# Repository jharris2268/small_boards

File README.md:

# small_boards
small breakout pcbs

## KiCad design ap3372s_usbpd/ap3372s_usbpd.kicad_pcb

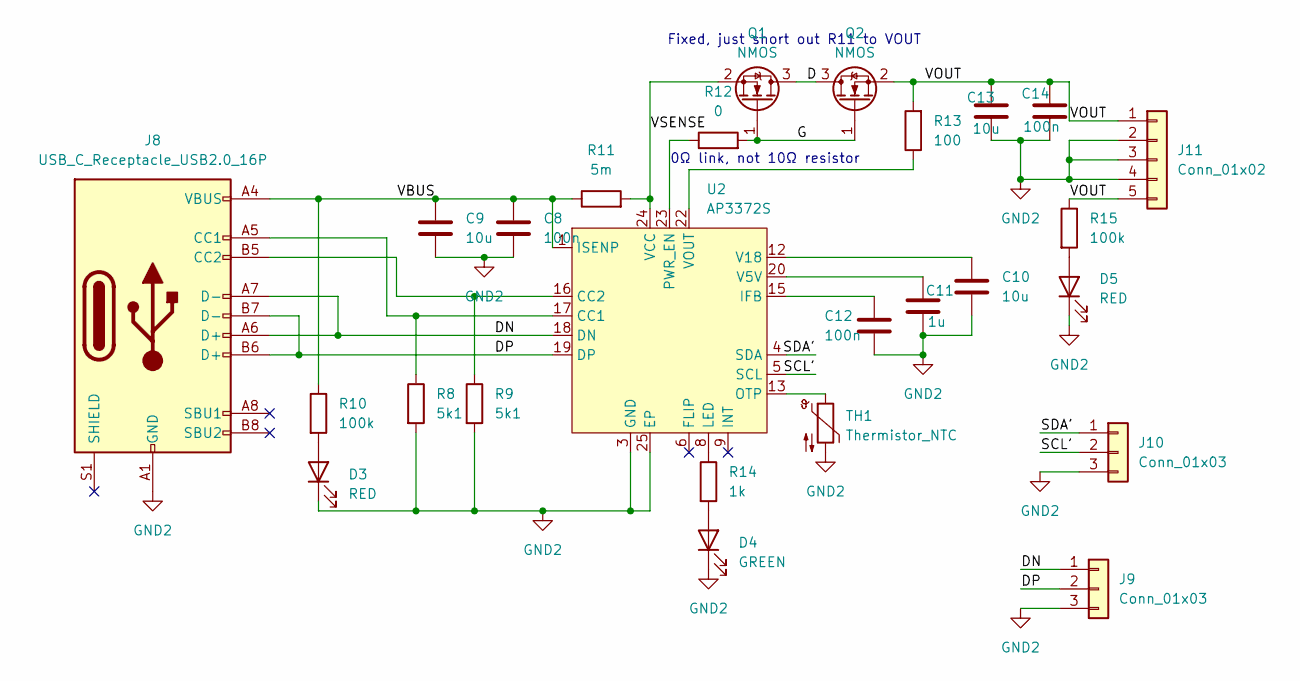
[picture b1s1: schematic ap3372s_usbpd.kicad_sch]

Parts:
C8, C12, C14: 100n; C_0805_2012Metric_Pad1.18x1.45mm_HandSolder
C9, C13: 10u; C_1206_3216Metric_Pad1.33x1.80mm_HandSolder
C10: 10u; C_0805_2012Metric_Pad1.18x1.45mm_HandSolder
C11: 1u; C_0805_2012Metric_Pad1.18x1.45mm_HandSolder
D3, D5: RED; LED_0805_2012Metric_Pad1.15x1.40mm_HandSolder
D4: GREEN; LED_0805_2012Metric_Pad1.15x1.40mm_HandSolder
J8: USB_C_Receptacle_USB2.0_16P; usb_c_connector
J9, J10: Conn_01x03; PinHeader_1x03_P2.54mm_Vertical
J11: Conn_01x02; PinHeader_1x05_P2.54mm_Vertical
Q1, Q2: NMOS; SOT-23
R8, R9: 5k1; R_0805_2012Metric_Pad1.20x1.40mm_HandSolder
R10, R15: 100k; R_0805_2012Metric_Pad1.20x1.40mm_HandSolder
R11: 5m; R_2512_6332Metric_Pad1.40x3.35mm_HandSolder
R12: 0; R_0805_2012Metric_Pad1.20x1.40mm_HandSolder
R13: 100; R_0805_2012Metric_Pad1.20x1.40mm_HandSolder
R14: 1k; R_0805_2012Metric_Pad1.20x1.40mm_HandSolder
TH1: Thermistor_NTC; R_0805_2012Metric_Pad1.20x1.40mm_HandSolder
U2: AP3372S; QFN-24-1EP_4x4mm_P0.5mm_EP2.6x2.6mm

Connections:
/D: Q1.3 (D), Q2.3 (D)
/DN: J8.A6 (D+), J8.A7 (D-), J9.1, U2.18 (DN)
/DP: J8.B6 (D+), J8.B7 (D-), J9.2, U2.19 (DP)
/G: Q1.1 (G), Q2.1 (G), R12.2
/SCL': J10.2, U2.5 (SCL)
/SDA': J10.1, U2.4 (SDA)
/VBUS: C8.1, C9.1, J8.A4 (VBUS), J8.A9 (VBUS), J8.B4 (VBUS), J8.B9 (VBUS), R10.1, R11.1, U2.1 (ISENP)
/VOUT: C13.1, C14.1, J11.1, J11.5, Q2.2 (S), R13.2, R15.1
/VSENSE: Q1.2 (S), R11.2, U2.24 (VCC)
GND2: C8.2, C9.2, C10.2, C11.2, C12.2, C13.2, C14.2, D3.1 (K), D4.1 (K), D5.1 (K), J8.A1 (GND), J8.A12 (GND), J8.B1 (GND), J8.B12 (GND), J9.3, J10.3, J11.2, J11.3, J11.4, R8.2, R9.2, TH1.2, U2.3 (GND), U2.25 (EP)
unnamed: D3.2 (A), R10.2
unnamed: D4.2 (A), R14.2
unnamed: D5.2 (A), R15.2
unnamed: J8.A5 (CC1), R8.1, U2.17 (CC1)
unnamed: J8.B5 (CC2), R9.1, U2.16 (CC2)
unnamed: C12.1, U2.15 (IFB)
unnamed: R14.1, U2.8 (LED)
unnamed: TH1.1, U2.13 (OTP)
unnamed: R12.1, U2.23 (PWR_EN)
unnamed: C11.1, U2.20 (V5V)
unnamed: C10.1, U2.12 (V18)
unnamed: R13.1, U2.22 (VOUT)

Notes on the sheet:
Fixed, just short out R11 to VOUT
0Ω link, not 10Ω resistor

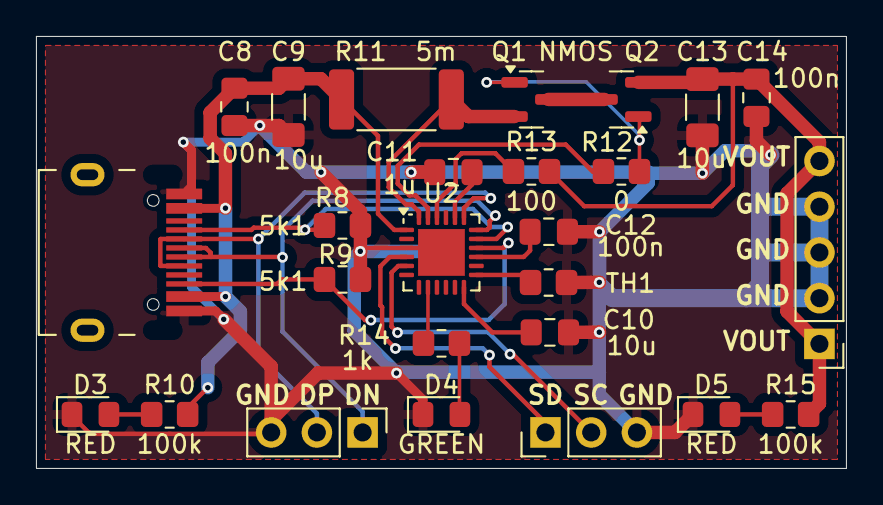
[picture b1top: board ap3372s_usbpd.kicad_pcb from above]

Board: 2 copper layers, 45.0 x 24.0 mm, 26 parts (0 on the bottom side), 22 nets.

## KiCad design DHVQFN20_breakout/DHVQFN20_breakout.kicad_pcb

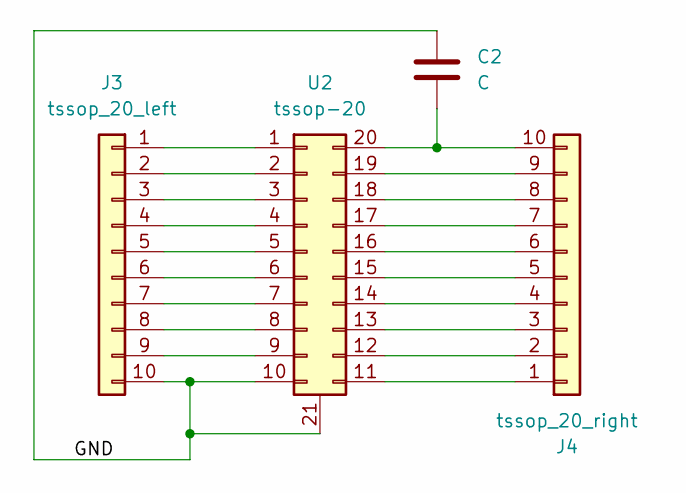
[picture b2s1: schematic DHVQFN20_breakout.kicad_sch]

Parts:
C2: C; C_0805_2012Metric_Pad1.18x1.45mm_HandSolder
J3: tssop_20_left; PinHeader_1x10_P2.54mm_Vertical
J4: tssop_20_right; PinHeader_1x10_P2.54mm_Vertical
U2: tssop-20; DHVQFN-20-1EP_2.5x4.5mm_P0.5mm_EP1x3mm

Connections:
/GND: C2.1, J3.10, U2.10, U2.21
unnamed: J3.1, U2.1
unnamed: J3.2, U2.2
unnamed: J3.3, U2.3
unnamed: J3.4, U2.4
unnamed: J3.5, U2.5
unnamed: J3.6, U2.6
unnamed: J3.7, U2.7
unnamed: J3.8, U2.8
unnamed: J3.9, U2.9
unnamed: J4.1, U2.11
unnamed: J4.2, U2.12
unnamed: J4.3, U2.13
unnamed: J4.4, U2.14
unnamed: J4.5, U2.15
unnamed: J4.6, U2.16
unnamed: J4.7, U2.17
unnamed: J4.8, U2.18
unnamed: J4.9, U2.19
unnamed: C2.2, J4.10, U2.20

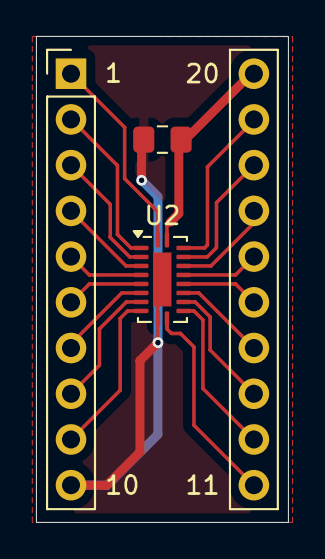
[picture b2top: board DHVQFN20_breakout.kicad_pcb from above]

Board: 2 copper layers, 14.0 x 27.0 mm, 4 parts (0 on the bottom side), 20 nets.

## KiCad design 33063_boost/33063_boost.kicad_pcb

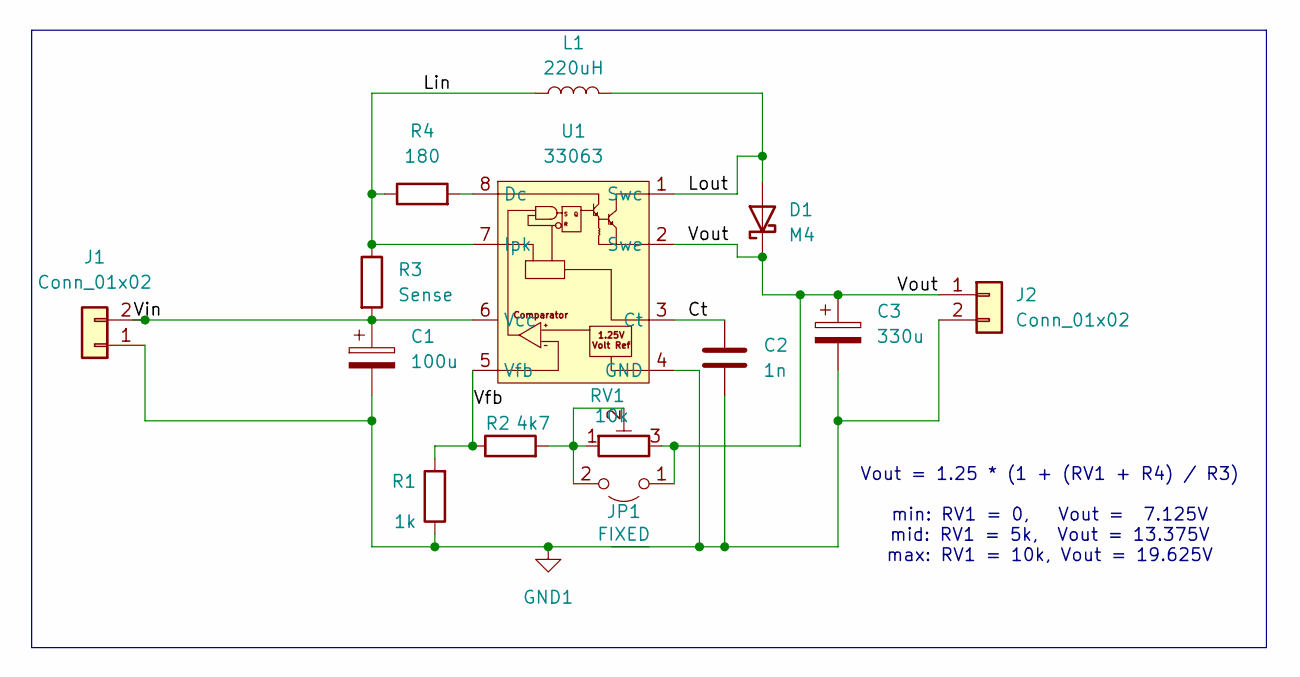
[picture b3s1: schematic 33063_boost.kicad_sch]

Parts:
C1: 100u; CP_Radial_D6.3mm_P2.50mm
C2: 1n; C_0805_2012Metric_Pad1.18x1.45mm_HandSolder
C3: 330u; CP_Radial_D6.3mm_P2.50mm
D1: M4; D_SMA_Handsoldering_with_symbol
J1, J2: Conn_01x02; sip_edge_2_no_slot
JP1: FIXED; SolderJumper-2_P1.3mm_Open_RoundedPad1.0x1.5mm
L1: 220uH; Inductor_CD54
R1: 1k; R_0805_2012Metric_Pad1.20x1.40mm_HandSolder
R2: 4k7; R_0805_2012Metric_Pad1.20x1.40mm_HandSolder
R3: Sense; LED_0805_2012Metric_Pad1.15x1.40mm_HandSolder
R4: 180; R_0805_2012Metric_Pad1.20x1.40mm_HandSolder
RV1: 10k; Potentiometer_Bourns_3296W_Vertical
U1: 33063; SOIC-8_3.9x4.9mm_P1.27mm

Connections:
/Ct: C2.1, U1.3 (Ct)
/Lin: L1.1, R3.1, R4.1, U1.7 (Ipk)
/Lout: D1.2 (A), L1.2, U1.1 (Swc)
/Vfb: R1.2, R2.1, U1.5 (Vfb)
/Vin: C1.1, J1.2, R3.2, U1.6 (Vcc)
/Vout: C3.1, D1.1 (K), J2.1, JP1.1 (A), RV1.3, U1.2 (Swe)
GND1: C1.2, C2.2, C3.2, J1.1, J2.2, R1.1, U1.4 (GND)
unnamed: JP1.2 (B), R2.2, RV1.1, RV1.2
unnamed: R4.2, U1.8 (Dc)

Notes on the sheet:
Vout = 1.25 * (1 + (RV1 + R4) / R3) min: RV1 = 0, Vout = 7.125V mid: RV1 = 5k, Vout = 13.375V max: RV1 = 10k, Vout = 19.625V

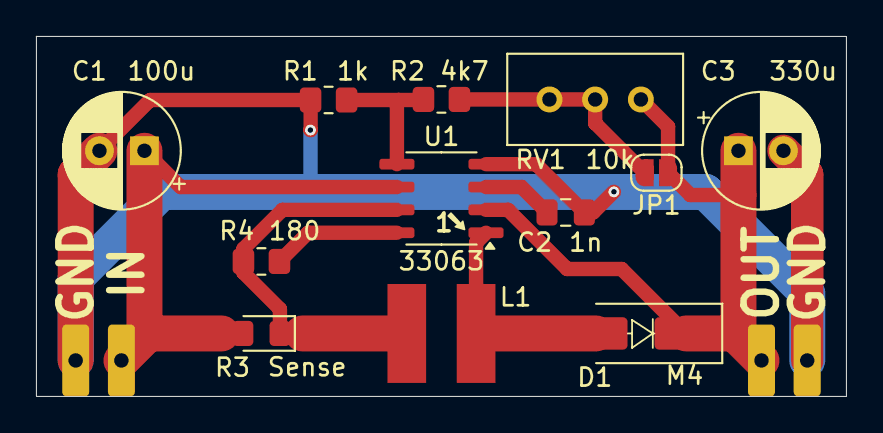
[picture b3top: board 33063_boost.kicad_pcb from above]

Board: 2 copper layers, 45.0 x 20.0 mm, 14 parts (0 on the bottom side), 9 nets.

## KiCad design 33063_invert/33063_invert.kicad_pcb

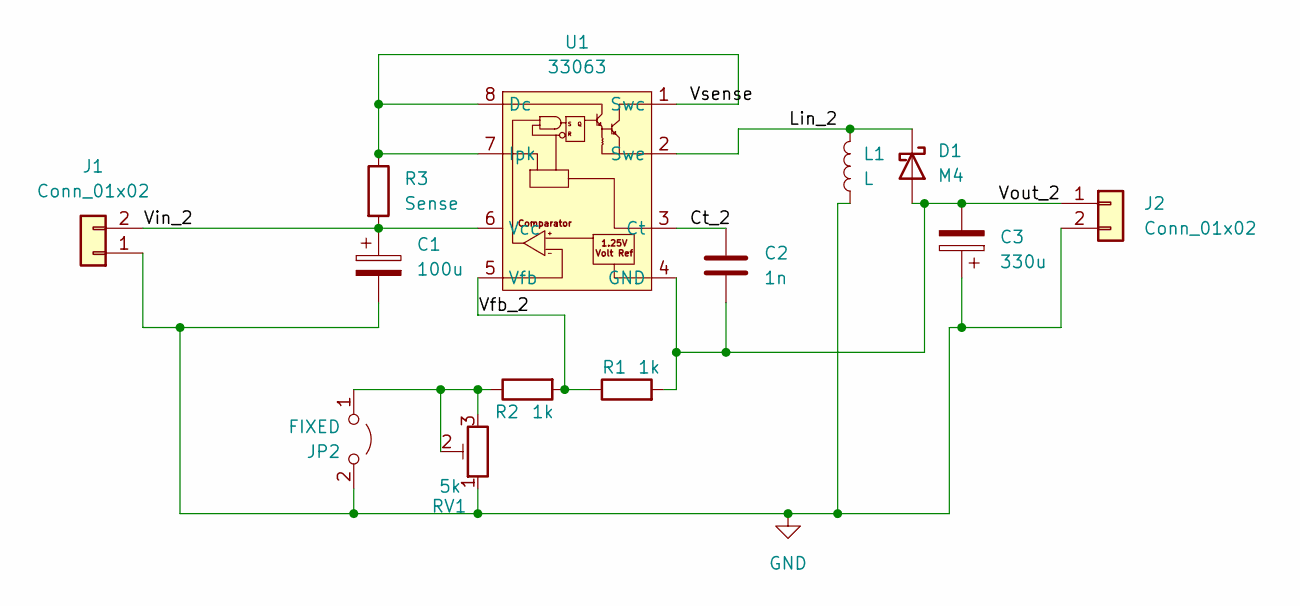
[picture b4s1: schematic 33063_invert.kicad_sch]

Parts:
C1: 100u; CP_Radial_D6.3mm_P2.50mm
C2: 1n; C_0805_2012Metric_Pad1.18x1.45mm_HandSolder
C3: 330u; CP_Radial_D6.3mm_P2.50mm
D1: M4; D_SMA_Handsoldering_with_symbol
J1, J2: Conn_01x02; sip_edge_2_no_slot
JP2: FIXED; SolderJumper-2_P1.3mm_Open_RoundedPad1.0x1.5mm
L1: L; Inductor_CD54
R1, R2: 1k; R_0805_2012Metric_Pad1.20x1.40mm_HandSolder
R3: Sense; R_0805_2012Metric_Pad1.20x1.40mm_HandSolder
RV1: 5k; Potentiometer_Bourns_3296W_Vertical
U1: 33063; SOIC-8_3.9x4.9mm_P1.27mm

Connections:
/Ct_2: C2.1, U1.3 (Ct)
/Lin_2: D1.1 (K), L1.2, U1.2 (Swe)
/Vfb_2: R1.1, R2.2, U1.5 (Vfb)
/Vin_2: C1.1, J1.2, R3.2, U1.6 (Vcc)
/Vout_2: C2.2, C3.2, D1.2 (A), J2.1, R1.2, U1.4 (GND)
/Vsense: R3.1, U1.1 (Swc), U1.7 (Ipk), U1.8 (Dc)
GND: C1.2, C3.1, J1.1, J2.2, JP2.2 (B), L1.1, RV1.1
unnamed: JP2.1 (A), R2.1, RV1.2, RV1.3

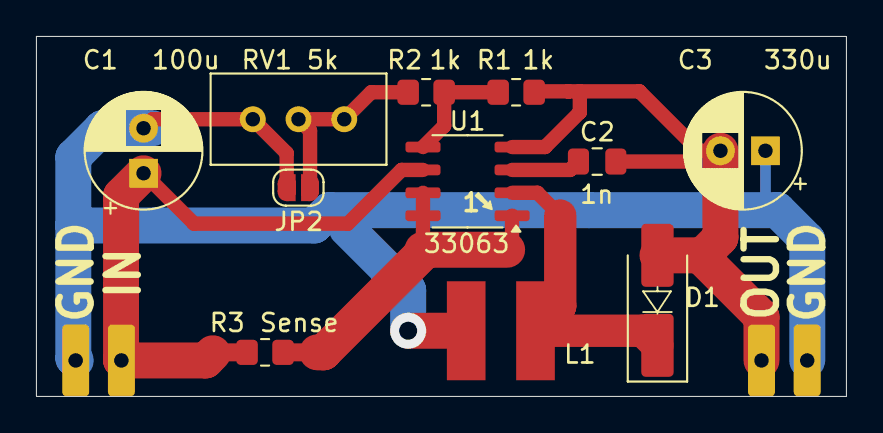
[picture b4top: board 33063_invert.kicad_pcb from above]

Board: 2 copper layers, 45.0 x 20.0 mm, 13 parts (0 on the bottom side), 8 nets.

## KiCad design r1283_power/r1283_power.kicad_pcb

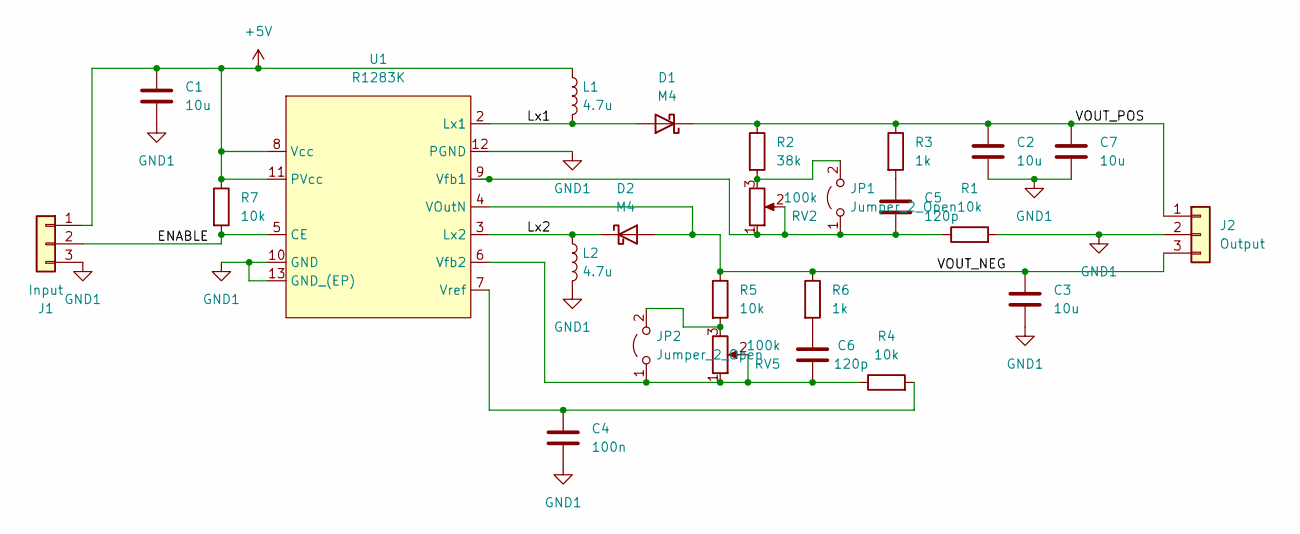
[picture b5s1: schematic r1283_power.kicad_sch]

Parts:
C1, C2, C3, C7: 10u; C_0805_2012Metric_Pad1.18x1.45mm_HandSolder
C4: 100n; C_0805_2012Metric_Pad1.18x1.45mm_HandSolder
C5, C6: 120p; C_0805_2012Metric_Pad1.18x1.45mm_HandSolder
D1, D2: M4; D_SMA_Handsoldering
J1: Input; sip_edge_3
J2: Output; sip_edge_3
JP1, JP2: Jumper_2_Open; SolderJumper-2_P1.3mm_Open_RoundedPad1.0x1.5mm
L1, L2: 4.7u; L_Wuerth_HCI-5040
R1, R4, R5, R7: 10k; R_0805_2012Metric_Pad1.20x1.40mm_HandSolder
R2: 38k; R_0805_2012Metric_Pad1.20x1.40mm_HandSolder
R3, R6: 1k; R_0805_2012Metric_Pad1.20x1.40mm_HandSolder
RV2, RV5: 100k; Potentiometer_Bourns_3296W_Vertical
U1: R1283K; DFN-12-1EP_3x3mm_P0.5mm_EP1.6x2.5mm

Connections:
+5V: C1.1, J1.1, L1.1, R7.1, U1.8 (Vcc), U1.11 (PVcc)
/ENABLE: J1.2, R7.2, U1.5 (CE)
/Lx1: D1.2 (A), L1.2, U1.2 (Lx1)
/Lx2: D2.1 (K), L2.1, U1.3 (Lx2)
/VOUT_NEG: C3.1, D2.2 (A), J2.3, R5.1, R6.1, U1.4 (VOutN)
/VOUT_POS: C2.1, C7.1, D1.1 (K), J2.1, R2.1, R3.1
GND1: C1.2, C2.2, C3.2, C4.2, C7.2, J1.3, J2.2, L2.2, R1.2, U1.10 (GND), U1.12 (PGND), U1.13 (GND_(EP))
unnamed: C5.1, R3.2
unnamed: C6.1, R6.2
unnamed: C5.2, JP1.1 (A), R1.1, RV2.1, RV2.2, U1.9 (Vfb1)
unnamed: JP1.2 (B), R2.2, RV2.3
unnamed: C6.2, JP2.1 (A), R4.1, RV5.1, RV5.2, U1.6 (Vfb2)
unnamed: JP2.2 (B), R5.2, RV5.3
unnamed: C4.1, R4.2, U1.7 (Vref)

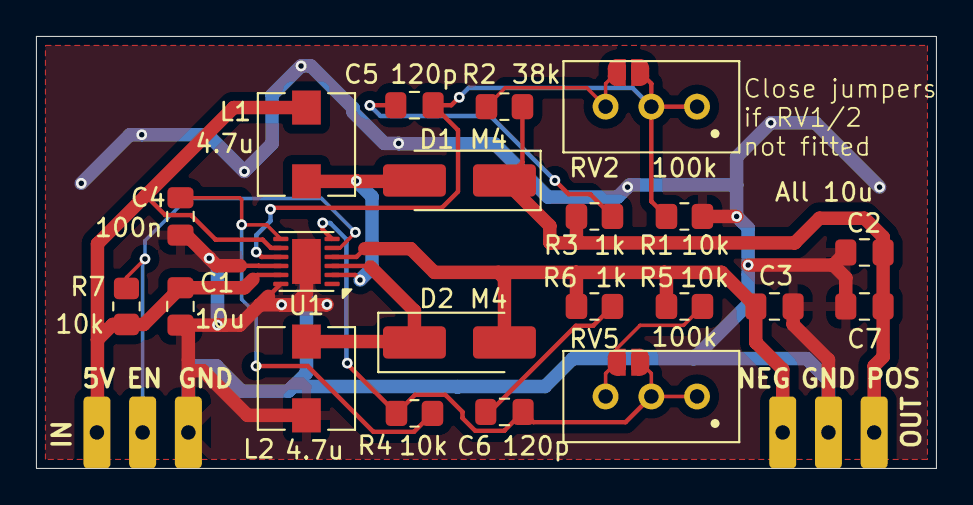
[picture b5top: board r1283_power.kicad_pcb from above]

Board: 2 copper layers, 50.0 x 24.0 mm, 25 parts (1 on the bottom side), 14 nets.

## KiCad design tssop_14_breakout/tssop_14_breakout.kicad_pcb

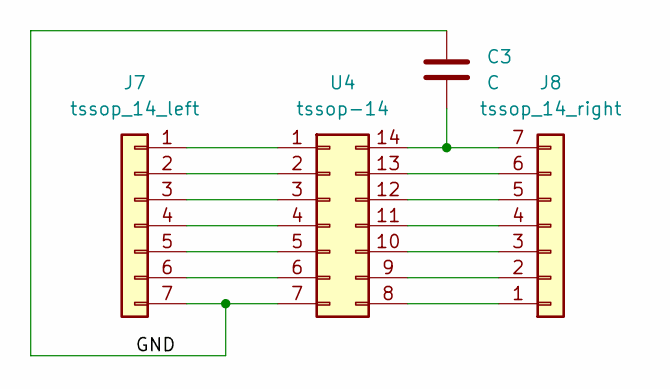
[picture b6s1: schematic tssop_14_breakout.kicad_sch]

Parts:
C3: C; C_0805_2012Metric_Pad1.18x1.45mm_HandSolder
J7: tssop_14_left; PinHeader_1x07_P2.54mm_Vertical
J8: tssop_14_right; PinHeader_1x07_P2.54mm_Vertical
U4: tssop-14; TSSOP-14_4.4x5mm_P0.65mm

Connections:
/GND: C3.1, J7.7, U4.7
unnamed: J7.1, U4.1
unnamed: J7.2, U4.2
unnamed: J7.3, U4.3
unnamed: J7.4, U4.4
unnamed: J7.5, U4.5
unnamed: J7.6, U4.6
unnamed: J8.1, U4.8
unnamed: J8.2, U4.9
unnamed: J8.3, U4.10
unnamed: J8.4, U4.11
unnamed: J8.5, U4.12
unnamed: J8.6, U4.13
unnamed: C3.2, J8.7, U4.14

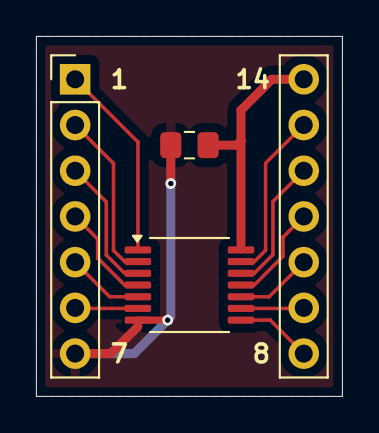
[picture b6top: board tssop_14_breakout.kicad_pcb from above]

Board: 2 copper layers, 17.0 x 20.0 mm, 4 parts (0 on the bottom side), 14 nets.

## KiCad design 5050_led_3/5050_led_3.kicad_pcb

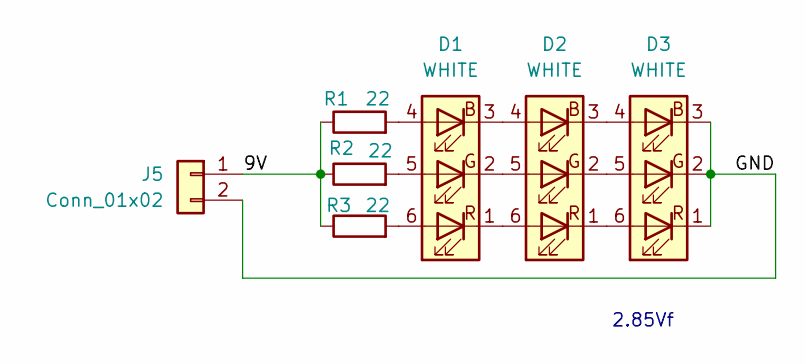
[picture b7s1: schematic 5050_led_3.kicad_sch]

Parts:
D1, D2, D3: WHITE; LED_RGB_5050-6
J5: Conn_01x02; sip_edge_2_no_slot
R1, R2, R3: 22; R_0805_2012Metric_Pad1.20x1.40mm_HandSolder

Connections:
/9V: J5.1, R1.1, R2.1, R3.1
/GND: D3.1 (RK), D3.2 (GK), D3.3 (BK), J5.2
unnamed: D1.4 (BA), R1.2
unnamed: D1.3 (BK), D2.4 (BA)
unnamed: D1.5 (GA), R2.2
unnamed: D1.2 (GK), D2.5 (GA)
unnamed: D1.6 (RA), R3.2
unnamed: D1.1 (RK), D2.6 (RA)
unnamed: D2.3 (BK), D3.4 (BA)
unnamed: D2.2 (GK), D3.5 (GA)
unnamed: D2.1 (RK), D3.6 (RA)

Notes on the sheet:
2.85Vf

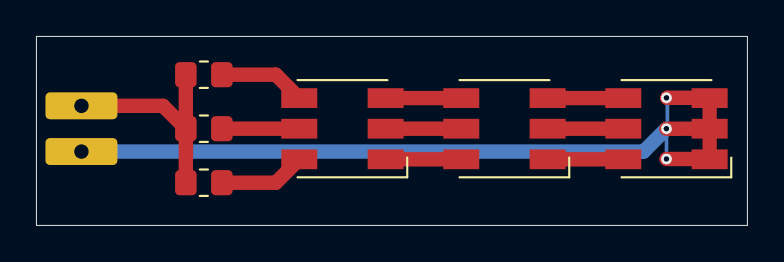
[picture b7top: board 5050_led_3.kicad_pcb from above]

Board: 2 copper layers, 39.5 x 10.5 mm, 7 parts (0 on the bottom side), 11 nets.

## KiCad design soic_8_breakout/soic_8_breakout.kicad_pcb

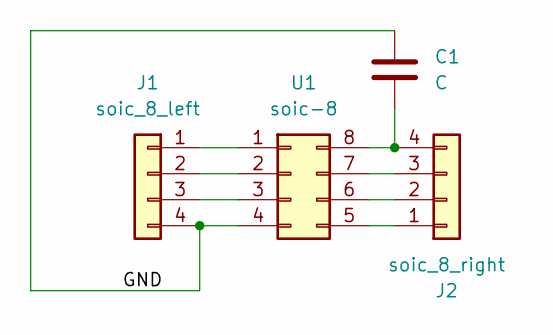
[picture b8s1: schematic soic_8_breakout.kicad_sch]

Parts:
C1: C; C_0805_2012Metric_Pad1.18x1.45mm_HandSolder
J1: soic_8_left; PinHeader_1x04_P2.54mm_Vertical
J2: soic_8_right; PinHeader_1x04_P2.54mm_Vertical
U1: soic-8; SOIC-8_3.9x4.9mm_P1.27mm

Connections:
/GND: C1.1, J1.4, U1.4
unnamed: J1.1, U1.1
unnamed: J1.2, U1.2
unnamed: J1.3, U1.3
unnamed: J2.1, U1.5
unnamed: J2.2, U1.6
unnamed: J2.3, U1.7
unnamed: C1.2, J2.4, U1.8

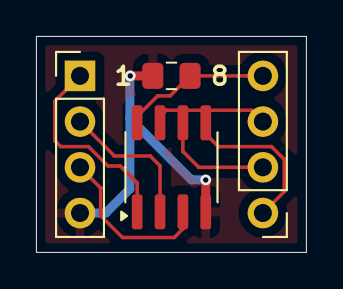
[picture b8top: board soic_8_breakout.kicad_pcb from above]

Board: 2 copper layers, 15.0 x 12.0 mm, 4 parts (0 on the bottom side), 8 nets.

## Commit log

2025-01-06 inital commit
2025-01-06 added gerbers
2025-01-06 copied in 33063 and led boards
2025-01-07 tidied up ap3372 board
2025-01-20 added DFN breakout changed trim pot type in 33063_boost, 33063_invert, r1283_power boards fixed error in 33063_boost board (move trim pot to higher side of voltage divider)
